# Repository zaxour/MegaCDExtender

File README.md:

# MegaCDExtender
A solution to allow for easier testing of Sega/Mega CD units

Ever had to troubleshoot a Mega CD? Everyone knows what a chore it can be to have to have the Genesis/MD sitting precariously above, making it difficult to probe the board. 

This is a simple extension board to allow for running the Genesis/MD off to the side, leaving the board open for analysis!

PCB's should be ordered in 1.6mm thickness. HASL is fine, ENIG would be a better choice. Make sure to do beveling for the CD side PCB.

*** USE THIS AT YOUR OWN RISK. I HAVE TESTED THIS AND IT WORKS PERFECTLY, BUT I AM NOT RESPONSIBLE FOR IMPROPER ASSEMBLY CAUSING DAMAGE ***

## Materials Needed
1 MD Side PCB

1 CD Side PCB 

4 60 (2x30) pin IDC connectors (https://www.aliexpress.us/item/3256808989392536.html)

1 60 pin RIGHT ANGLE Card Edge Connector (notches should be oriented like the photo) (https://www.aliexpress.us/item/3256803460752665.html)

2 60 pin IDC cables (https://www.aliexpress.us/item/3256809525176986.html)

## Assembly Instructions

### 1. Assemble the IDC and Card Edge connectors
Make sure the notches on the IDC connectors align with the indicated notch on the silkscreen.

### 2. Insert The First IDC cable as shown

### 3. Insert the Second IDC cable
This completes the assembly. It is recommended to verify pin to pin connectivity from the 60 pin slot on the MD side to the 60 pin edge on the CD side.

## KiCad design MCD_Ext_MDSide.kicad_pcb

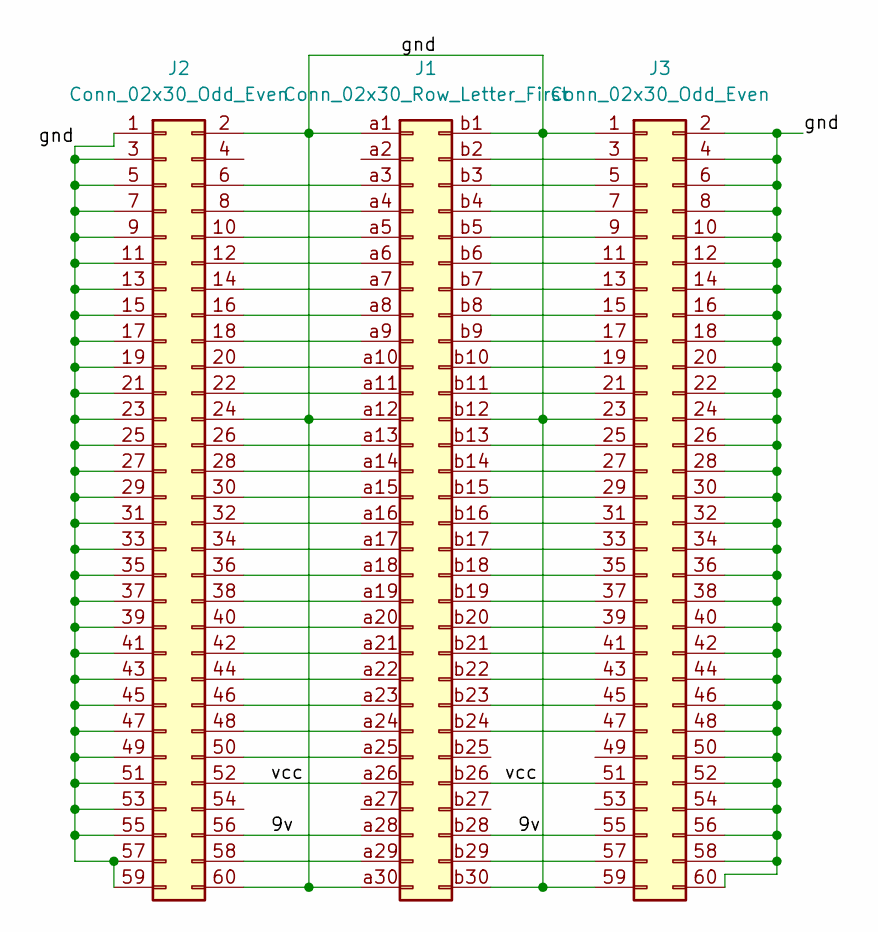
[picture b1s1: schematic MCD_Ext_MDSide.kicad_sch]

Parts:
J1: Conn_02x30_Row_Letter_First; Edge_60P
J2, J3: Conn_02x30_Odd_Even; IDC-Header_2x30_P2.54mm_Vertical

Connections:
/9v: J1.a28, J1.b28, J2.56, J3.55
/gnd: J1.a1, J1.a12, J1.a30, J1.b1, J1.b12, J1.b30, J2.1, J2.2, J2.3, J2.5, J2.7, J2.9, J2.11, J2.13, J2.15, J2.17, J2.19, J2.21, J2.23, J2.24, J2.25, J2.27, J2.29, J2.31, J2.33, J2.35, J2.37, J2.39, J2.41, J2.43, J2.45, J2.47, J2.49, J2.51, J2.53, J2.55, J2.57, J2.59, J2.60, J3.1, J3.2, J3.4, J3.6, J3.8, J3.10, J3.12, J3.14, J3.16, J3.18, J3.20, J3.22, J3.23, J3.24, J3.26, J3.28, J3.30, J3.32, J3.34, J3.36, J3.38, J3.40, J3.42, J3.44, J3.46, J3.48, J3.50, J3.52, J3.54, J3.56, J3.58, J3.59, J3.60
/vcc: J1.a26, J1.b26, J2.52, J3.51
unnamed: J1.a3, J2.6
unnamed: J1.a4, J2.8
unnamed: J1.a5, J2.10
unnamed: J1.a6, J2.12
unnamed: J1.a7, J2.14
unnamed: J1.a8, J2.16
unnamed: J1.a9, J2.18
unnamed: J1.a10, J2.20
unnamed: J1.a11, J2.22
unnamed: J1.a13, J2.26
unnamed: J1.a14, J2.28
unnamed: J1.a15, J2.30
unnamed: J1.a16, J2.32
unnamed: J1.a17, J2.34
unnamed: J1.a18, J2.36
unnamed: J1.a19, J2.38
unnamed: J1.a20, J2.40
unnamed: J1.a21, J2.42
unnamed: J1.a22, J2.44
unnamed: J1.a23, J2.46
unnamed: J1.a24, J2.48
unnamed: J1.a25, J2.50
unnamed: J1.a29, J2.58
unnamed: J1.b2, J3.3
unnamed: J1.b3, J3.5
unnamed: J1.b4, J3.7
unnamed: J1.b5, J3.9
unnamed: J1.b6, J3.11
unnamed: J1.b7, J3.13
unnamed: J1.b8, J3.15
unnamed: J1.b9, J3.17
unnamed: J1.b10, J3.19
unnamed: J1.b11, J3.21
unnamed: J1.b13, J3.25
unnamed: J1.b14, J3.27
unnamed: J1.b15, J3.29
unnamed: J1.b16, J3.31
unnamed: J1.b17, J3.33
unnamed: J1.b18, J3.35
unnamed: J1.b19, J3.37
unnamed: J1.b20, J3.39
unnamed: J1.b21, J3.41
unnamed: J1.b22, J3.43
unnamed: J1.b23, J3.45
unnamed: J1.b24, J3.47
unnamed: J1.b29, J3.57

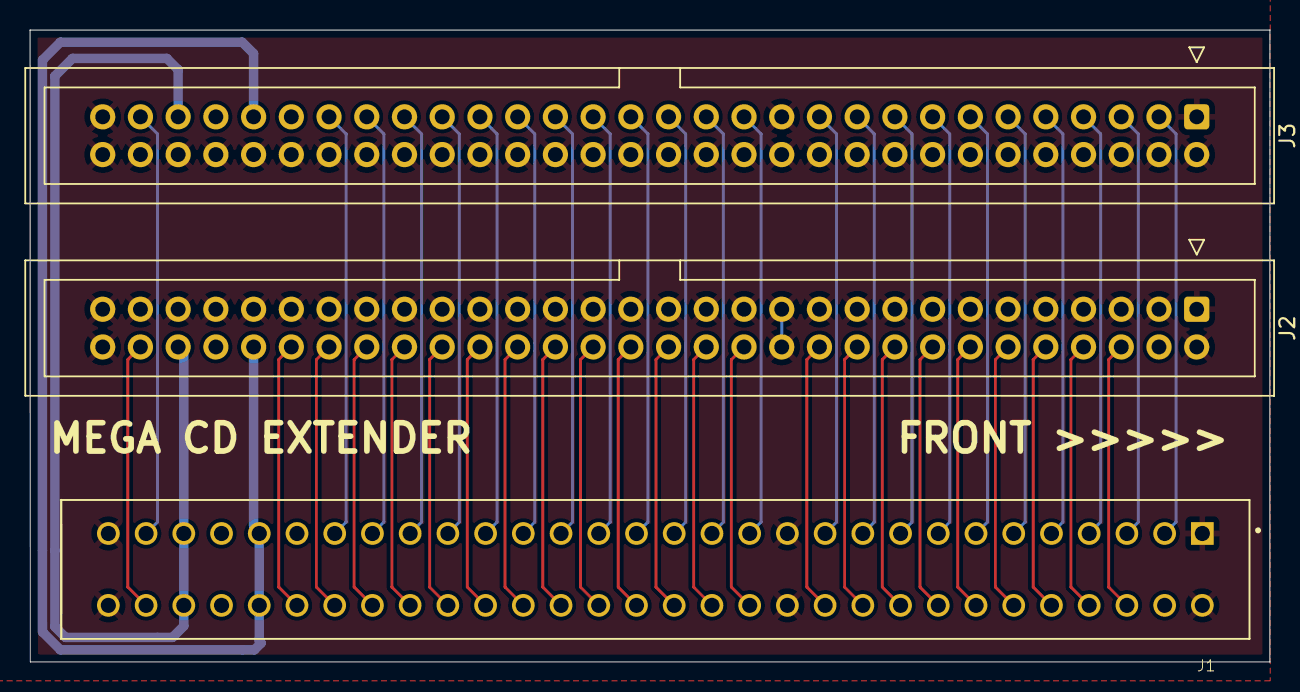
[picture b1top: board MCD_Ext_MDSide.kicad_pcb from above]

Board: 2 copper layers, 83.5 x 42.5 mm, 3 parts (0 on the bottom side), 49 nets.
